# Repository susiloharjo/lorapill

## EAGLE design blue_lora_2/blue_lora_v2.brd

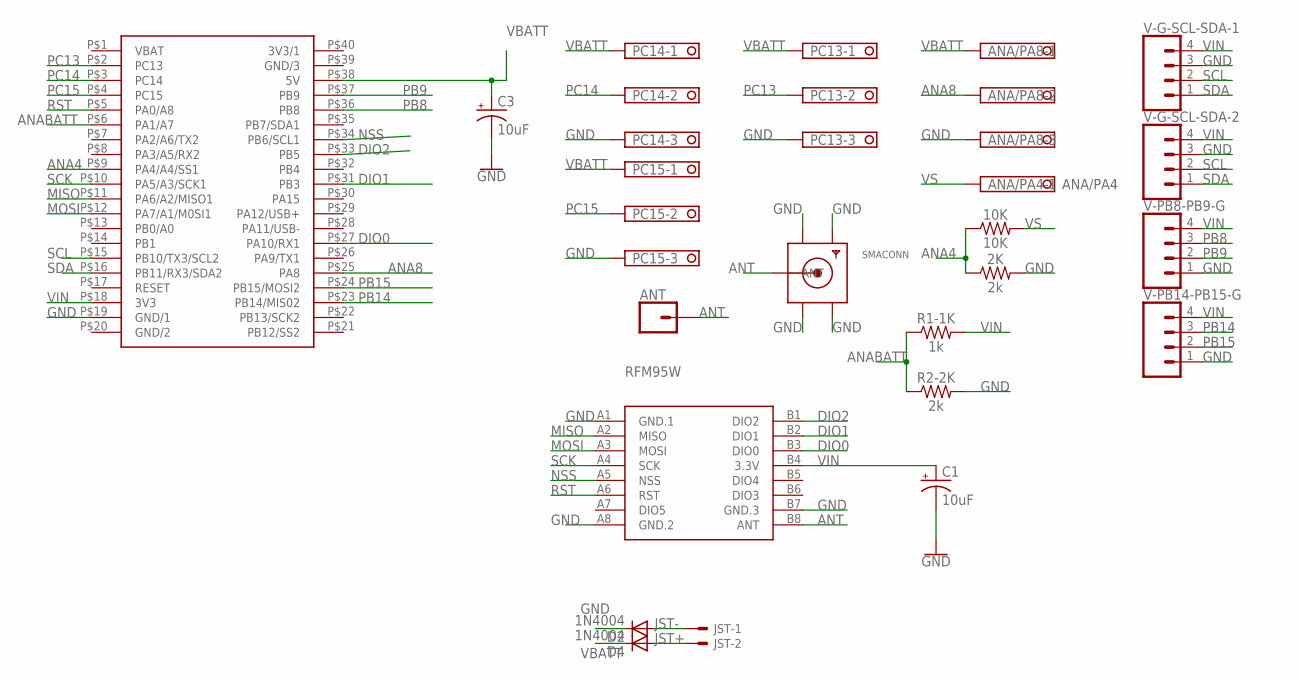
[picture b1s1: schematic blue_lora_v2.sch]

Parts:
2K: 2k; AXIAL-0.3-KIT
10K: 10K; AXIAL-0.3-KIT
ANA/PA4: ANA/PA4; TERMINAL-BLOCK-2-PIN-3.5MM-LONG-PAD
ANA/PA8: TERMINAL-BLOCK-3.5MM-3-PIN-LONG-PAD; TERMINAL-BLOCK-3-PIN-3.5MM-LONG-PAD
ANT: CONN_01; 1X01
C1, C3: 10uF; CPOL-RADIAL-2.5MM-5MM
D2, D4: 1N4004; DO41-10
JST: JST-XH-02-PIN-LONG-PAD; JST-XH-02-PACKAGE-LONG-PAD
PC13, PC14, PC15: TERMINAL-BLOCK-3.5MM-3-PIN-LONG-PAD; TERMINAL-BLOCK-3-PIN-3.5MM-LONG-PAD
R1-1K: 1k; AXIAL-0.3-KIT
R2-2K: 2k; AXIAL-0.3-KIT
RFM95W: WIRELESS-LORA-RFM95W#SMD
SMACONN: SMACONNECTOR_EDGE; SMA_EDGELAUNCH
U$2: BLUEPILL
V-G-SCL-SDA-1, V-G-SCL-SDA-2: CONN_04LOCK_LONGPADS; 1X04_LOCK_LONGPADS
V-PB8-PB9-G, V-PB14-PB15-G: CONN_04LOCK_LONGPADS; 1X04_LOCK_LONGPADS

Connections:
ANA4: 2K.P$1 (1), 10K.P$1 (1), U$2.P$9 (PA4/A4/SS1)
ANA8: ANA/PA8.2, U$2.P$25 (PA8)
ANABATT: R1-1K.P$1 (1), R2-2K.P$1 (1), U$2.P$6 (PA1/A7)
ANT: ANT.1, RFM95W.B8 (ANT), SMACONN.P (ANT)
DIO0: RFM95W.B3 (DIO0), U$2.P$27 (PA10/RX1)
DIO1: RFM95W.B2 (DIO1), U$2.P$31 (PB3)
DIO2: RFM95W.B1 (DIO2), U$2.P$33 (PB5)
GND: 2K.P$2 (2), ANA/PA8.3, C1.2 (-), C3.2 (-), D2.C, PC13.3, PC14.3, PC15.3, R2-2K.P$2 (2), RFM95W.A1 (GND.1), RFM95W.A8 (GND.2), RFM95W.B7 (GND.3), SMACONN.GND@1 (GND4), SMACONN.GND@2 (GND3), SMACONN.GND@3 (GND2), SMACONN.GND@4 (GND1), U$2.P$19 (GND/1), V-G-SCL-SDA-1.3, V-G-SCL-SDA-2.3, V-PB8-PB9-G.1, V-PB14-PB15-G.1
JST+: D4.A, JST.2
JST-: D2.A, JST.1
MISO: RFM95W.A2 (MISO), U$2.P$11 (PA6/A2/MISO1)
MOSI: RFM95W.A3 (MOSI), U$2.P$12 (PA7/A1/M0SI1)
NSS: RFM95W.A5 (NSS), U$2.P$34 (PB6/SCL1)
PB8: U$2.P$36 (PB8), V-PB8-PB9-G.3
PB9: U$2.P$37 (PB9), V-PB8-PB9-G.2
PB14: U$2.P$23 (PB14/MIS02), V-PB14-PB15-G.3
PB15: U$2.P$24 (PB15/MOSI2), V-PB14-PB15-G.2
PC13: PC13.2, U$2.P$2 (PC13)
PC14: PC14.2, U$2.P$3 (PC14)
PC15: PC15.2, U$2.P$4 (PC15)
RST: RFM95W.A6 (RST), U$2.P$5 (PA0/A8)
SCK: RFM95W.A4 (SCK), U$2.P$10 (PA5/A3/SCK1)
SCL: U$2.P$15 (PB10/TX3/SCL2), V-G-SCL-SDA-1.2, V-G-SCL-SDA-2.2
SDA: U$2.P$16 (PB11/RX3/SDA2), V-G-SCL-SDA-1.1, V-G-SCL-SDA-2.1
VBATT: ANA/PA8.1, C3.1 (+), D4.C, PC13.1, PC14.1, PC15.1, U$2.P$38 (5V)
VIN: C1.1 (+), R1-1K.P$2 (2), RFM95W.B4 (3.3V), U$2.P$18 (3V3), V-G-SCL-SDA-1.4, V-G-SCL-SDA-2.4, V-PB8-PB9-G.4, V-PB14-PB15-G.4
VS: 10K.P$2 (2), ANA/PA4.1

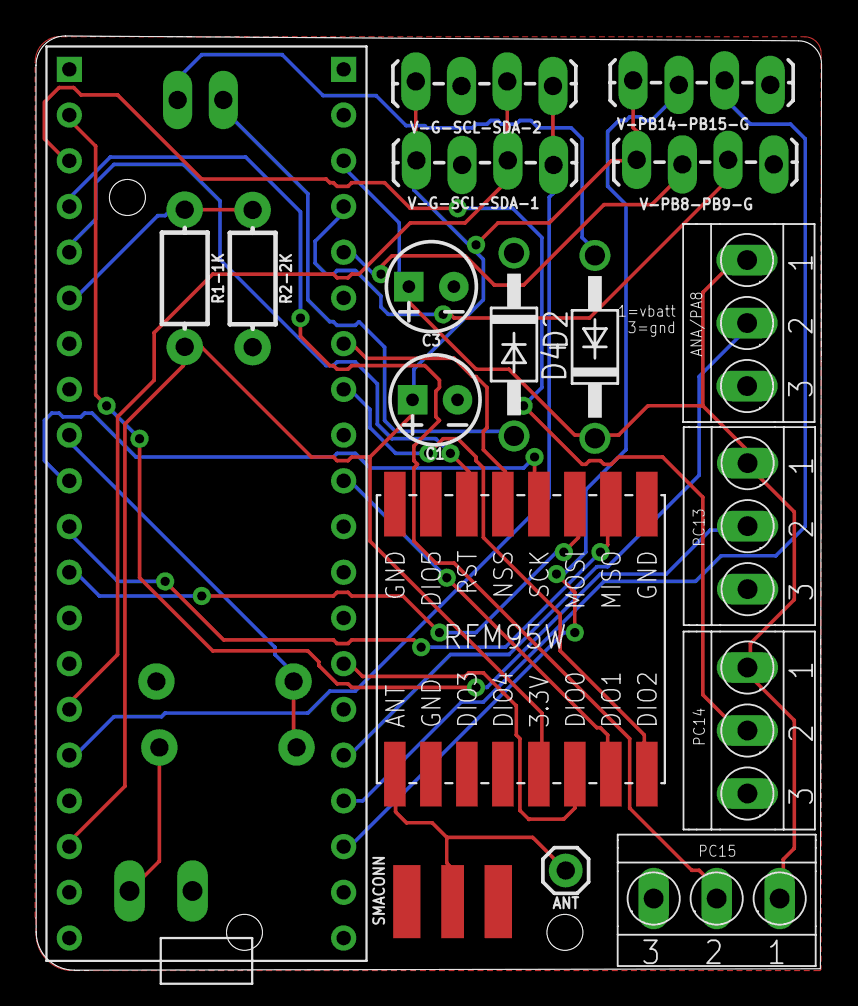
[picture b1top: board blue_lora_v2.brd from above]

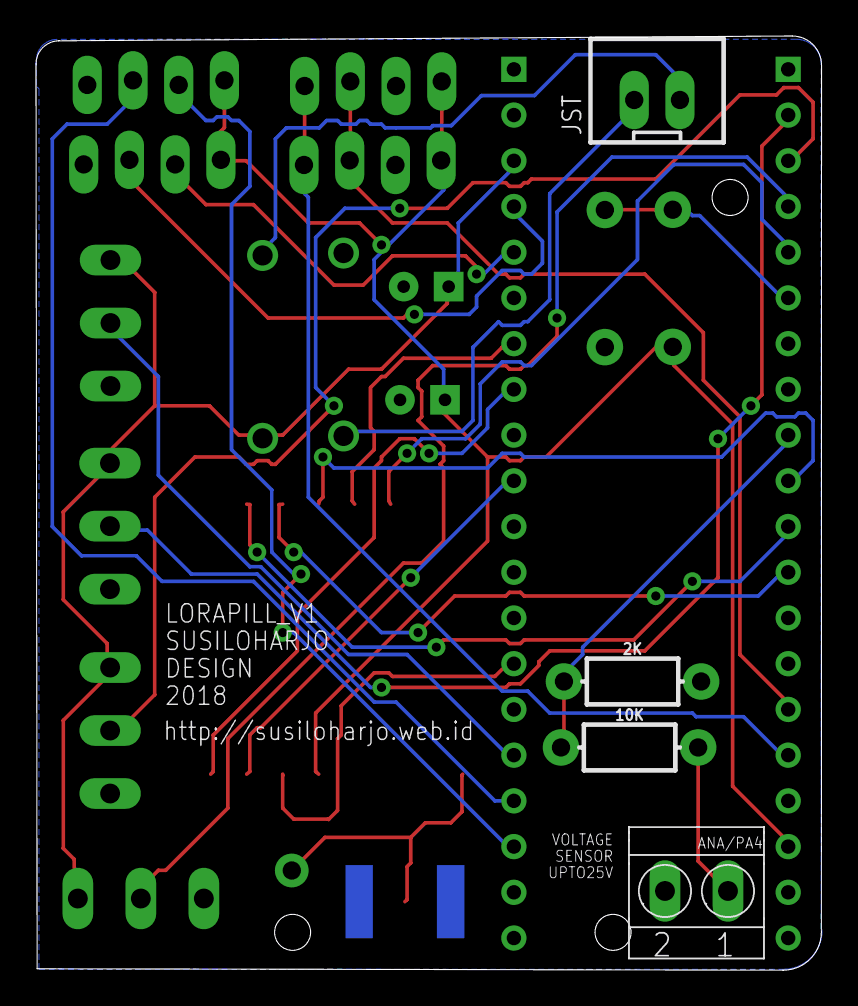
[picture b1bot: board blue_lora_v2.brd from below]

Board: 2 copper layers, 43.6 x 51.9 mm, 22 parts (4 on the bottom side), 27 nets.

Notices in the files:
parts and their libraries:
SparkFun-Capacitors: Licensing: Creative Commons ShareAlike 4.0 International - https://creativecommons.org/licenses/by-sa/4.0
diy-modules: Released under the Creative Commons Attribution 4.0 International License: http://creativecommons.org/licenses/by/4.0
